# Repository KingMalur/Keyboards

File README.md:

# Keyboards
My personal collection of PCB-designs for keyboards/macroboards. Made in KiCAD.

Untested PCB-designs are going to have a disclaimer in their respective README.

Naming according to this list:
https://www.worldwildlife.org/species/directory?direction=desc&sort=extinction_status

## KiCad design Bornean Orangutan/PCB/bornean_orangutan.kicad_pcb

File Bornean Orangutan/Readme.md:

# Bornean Orangutan
A minimal macroboard aimed to be smaller than 100mmx100mm to qualify for extremely cheap PCB-manufacturing (Since most offer a cheap deal for everything below these values). 

## This PCB is untested and probably not working as intended if at all.

See https://www.worldwildlife.org/species/bornean-orangutan for more information.

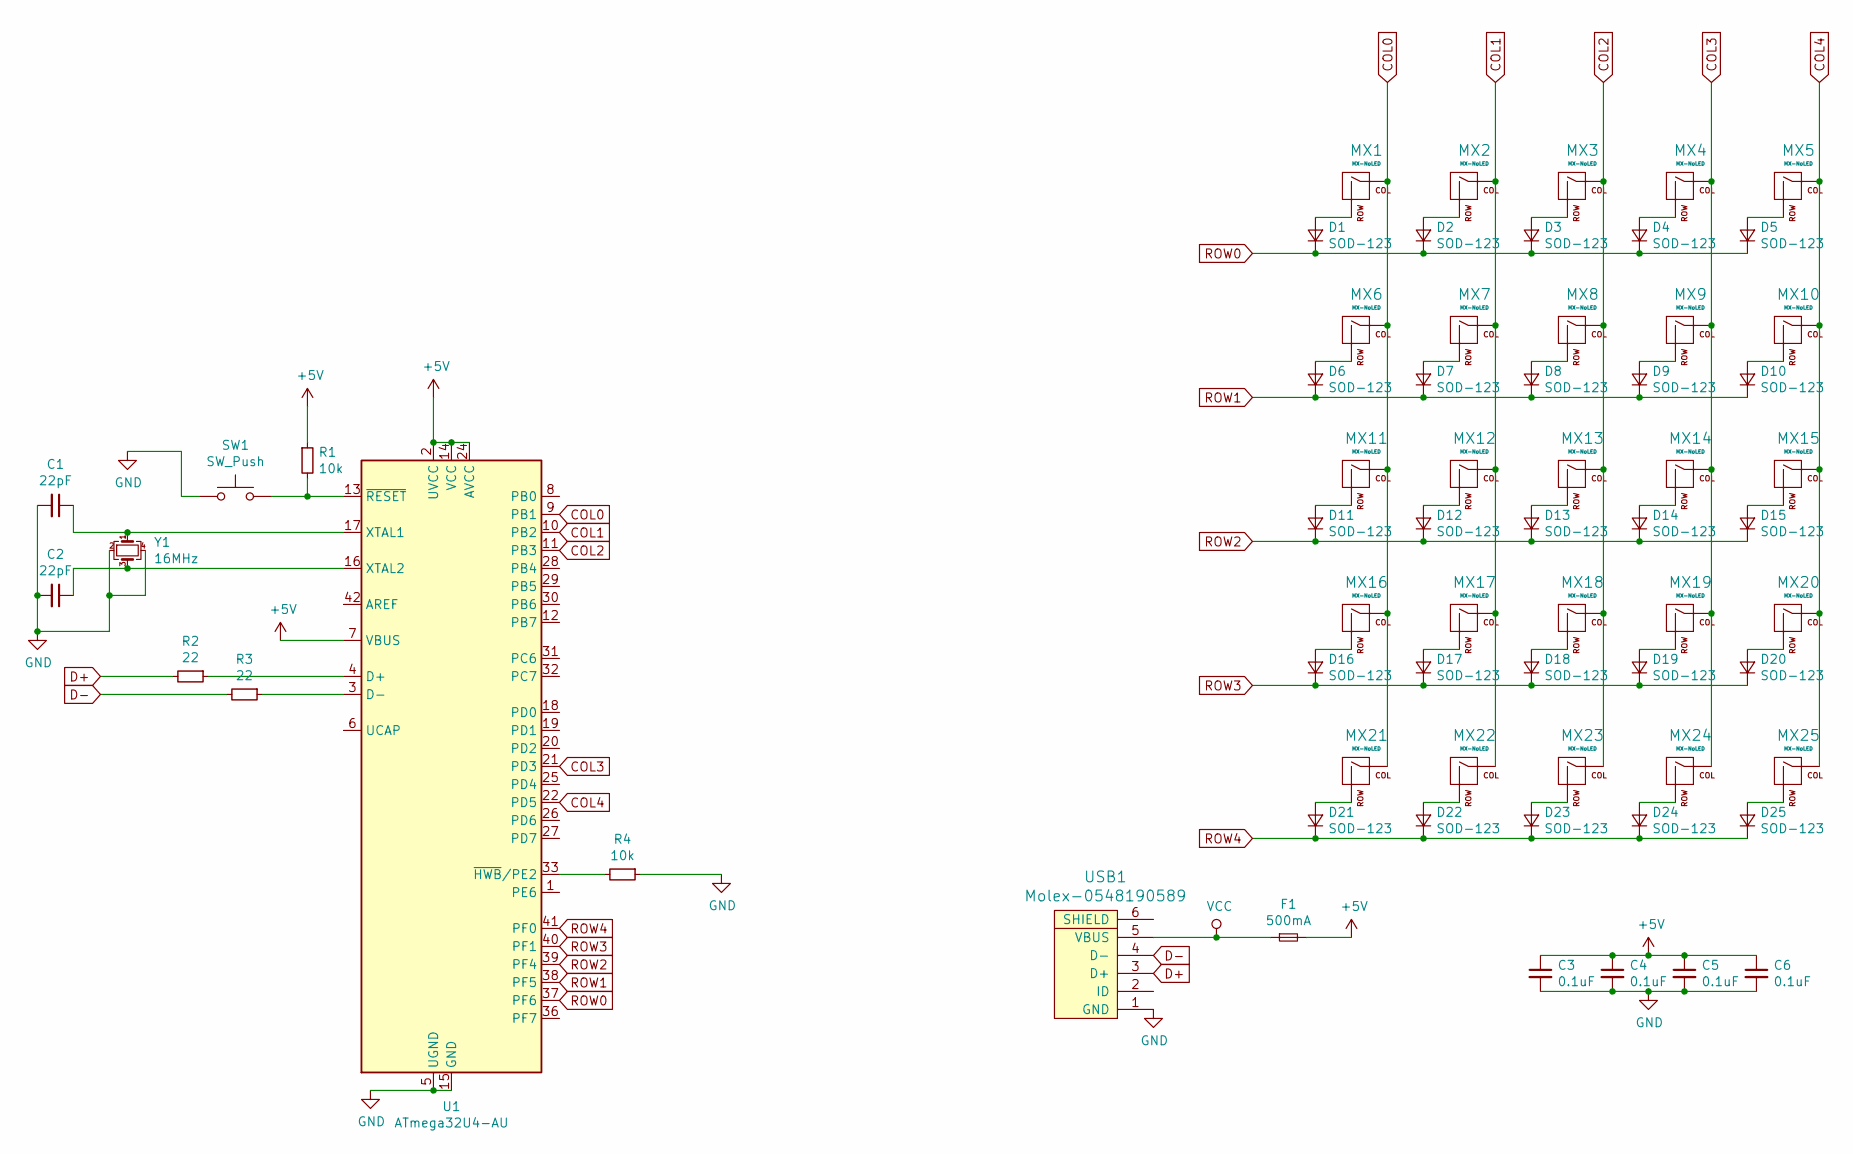
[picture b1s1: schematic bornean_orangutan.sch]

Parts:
C1, C2: 22pF; C_0805_2012Metric
C3, C4, C5, C6: 0.1uF; C_0805_2012Metric
D1, D2, D3, D4, D5, D6, D7, D8, D9, D10, D11, D12, D13, D14, D15, D16, D17, D18, D19, D20, D21, D22, D23, D24, D25: SOD-123; D_SOD-123
F1: 500mA; Fuse_1206_3216Metric
MX1, MX2, MX3, MX4, MX5, MX6, MX7, MX8, MX9, MX10, MX11, MX12, MX13, MX14, MX15, MX16, MX17, MX18, MX19, MX20, MX21, MX22, MX23, MX24, MX25: MX-NoLED; MX-1U
R1, R4: 10k; R_0805_2012Metric
R2, R3: 22; R_0805_2012Metric
SW1: SW_Push; SKQG-1155865
U1: ATmega32U4-AU; TQFP-44_10x10mm_P0.8mm
USB1: Molex-0548190589
Y1: 16MHz; Crystal_SMD_3225-4Pin_3.2x2.5mm

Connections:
+5V: C3.1, C4.1, C5.1, C6.1, F1.2, R1.1, U1.2 (UVCC), U1.7 (VBUS), U1.14 (VCC), U1.24 (AVCC), U1.34 (VCC), U1.44 (AVCC)
COL0: MX1.1 (COL), MX6.1 (COL), MX11.1 (COL), MX16.1 (COL), MX21.1 (COL), U1.9 (PB1)
COL1: MX2.1 (COL), MX7.1 (COL), MX12.1 (COL), MX17.1 (COL), MX22.1 (COL), U1.10 (PB2)
COL2: MX3.1 (COL), MX8.1 (COL), MX13.1 (COL), MX18.1 (COL), MX23.1 (COL), U1.11 (PB3)
COL3: MX4.1 (COL), MX9.1 (COL), MX14.1 (COL), MX19.1 (COL), MX24.1 (COL), U1.21 (PD3)
COL4: MX5.1 (COL), MX10.1 (COL), MX15.1 (COL), MX20.1 (COL), MX25.1 (COL), U1.22 (PD5)
D+: R2.2, USB1.3 (D+)
D-: R3.2, USB1.4 (D-)
GND: C1.2, C2.2, C3.2, C4.2, C5.2, C6.2, R4.1, SW1.1, U1.5 (UGND), U1.15 (GND), U1.23 (GND), U1.35 (GND), U1.43 (GND), USB1.1 (GND), Y1.2, Y1.4
unnamed: C1.1, U1.17 (XTAL1), Y1.1
unnamed: C2.1, U1.16 (XTAL2), Y1.3
unnamed: D1.2 (A), MX1.2 (ROW)
unnamed: D2.2 (A), MX2.2 (ROW)
unnamed: D3.2 (A), MX3.2 (ROW)
unnamed: D4.2 (A), MX4.2 (ROW)
unnamed: D5.2 (A), MX5.2 (ROW)
unnamed: D6.2 (A), MX6.2 (ROW)
unnamed: D7.2 (A), MX7.2 (ROW)
unnamed: D8.2 (A), MX8.2 (ROW)
unnamed: D9.2 (A), MX9.2 (ROW)
unnamed: D10.2 (A), MX10.2 (ROW)
unnamed: D11.2 (A), MX11.2 (ROW)
unnamed: D12.2 (A), MX12.2 (ROW)
unnamed: D13.2 (A), MX13.2 (ROW)
unnamed: D14.2 (A), MX14.2 (ROW)
unnamed: D15.2 (A), MX15.2 (ROW)
unnamed: D16.2 (A), MX16.2 (ROW)
unnamed: D17.2 (A), MX17.2 (ROW)
unnamed: D18.2 (A), MX18.2 (ROW)
unnamed: D19.2 (A), MX19.2 (ROW)
unnamed: D20.2 (A), MX20.2 (ROW)
unnamed: D21.2 (A), MX21.2 (ROW)
unnamed: D22.2 (A), MX22.2 (ROW)
unnamed: D23.2 (A), MX23.2 (ROW)
unnamed: D24.2 (A), MX24.2 (ROW)
unnamed: D25.2 (A), MX25.2 (ROW)
unnamed: R1.2, SW1.2, U1.13 (~RESET)
unnamed: R2.1, U1.4 (D+)
unnamed: R3.1, U1.3 (D-)
unnamed: R4.2, U1.33 (~HWB~/PE2)
ROW0: D1.1 (K), D2.1 (K), D3.1 (K), D4.1 (K), D5.1 (K), U1.37 (PF6)
ROW1: D6.1 (K), D7.1 (K), D8.1 (K), D9.1 (K), D10.1 (K), U1.38 (PF5)
ROW2: D11.1 (K), D12.1 (K), D13.1 (K), D14.1 (K), D15.1 (K), U1.39 (PF4)
ROW3: D16.1 (K), D17.1 (K), D18.1 (K), D19.1 (K), D20.1 (K), U1.40 (PF1)
ROW4: D21.1 (K), D22.1 (K), D23.1 (K), D24.1 (K), D25.1 (K), U1.41 (PF0)
VCC: F1.1, USB1.5 (VBUS)

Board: 2 copper layers, 65 parts (40 on the bottom side), 46 nets, no tracks yet.

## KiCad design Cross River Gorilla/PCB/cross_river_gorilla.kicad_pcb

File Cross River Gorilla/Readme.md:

# Cross River Gorilla
A 60% 5x14 keyboard (64 keys) in ISO-DE (not 100% - obviously - but close since I tried to copy my current 100% ISO-DE keyboard).

## This PCB is untested and probably not working as intended if at all.

See https://www.worldwildlife.org/species/cross-river-gorilla for more information.

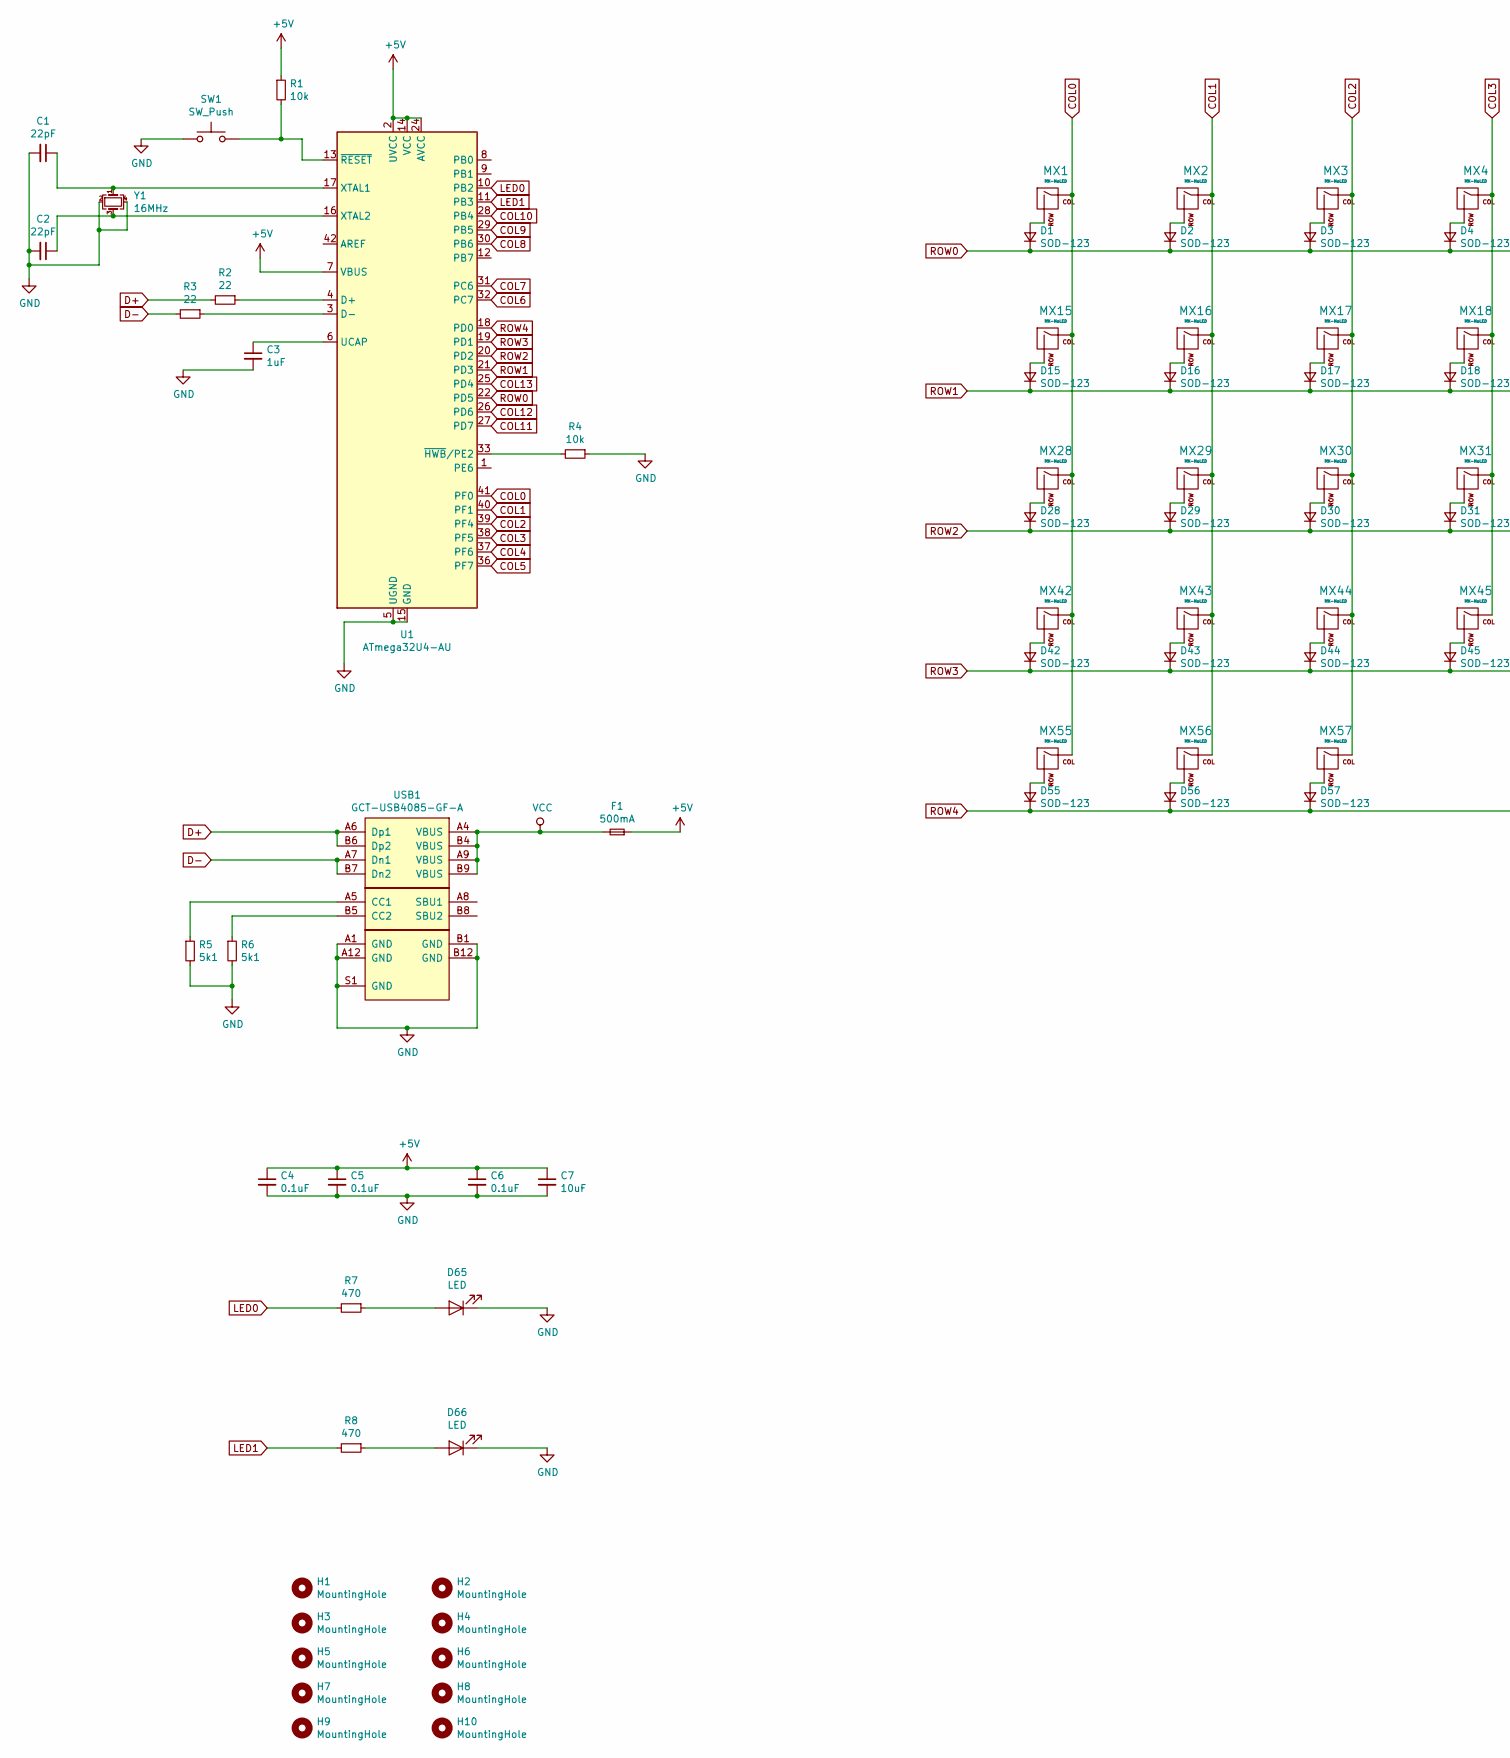
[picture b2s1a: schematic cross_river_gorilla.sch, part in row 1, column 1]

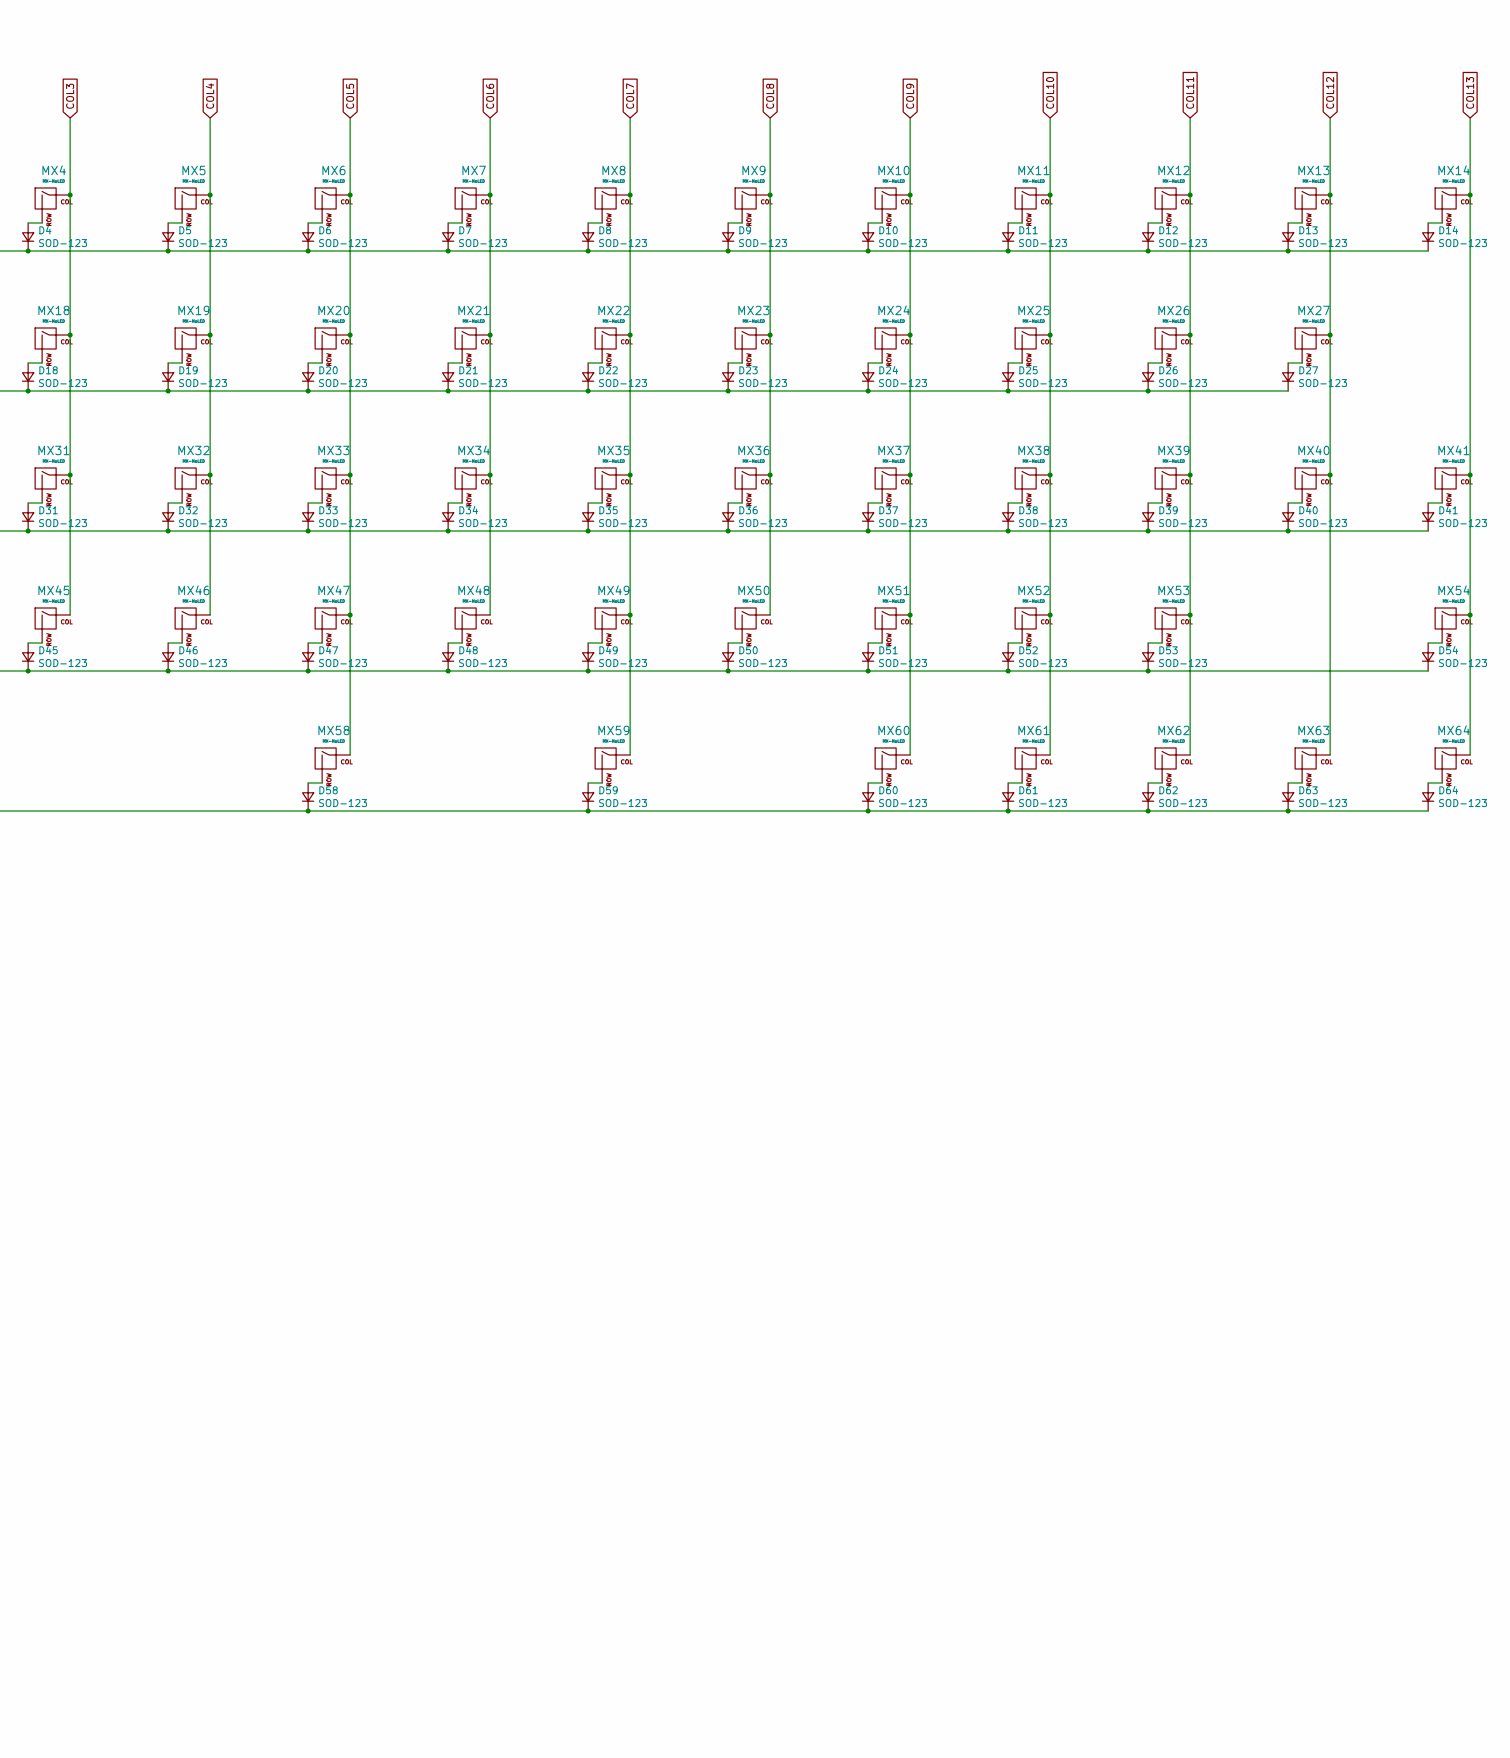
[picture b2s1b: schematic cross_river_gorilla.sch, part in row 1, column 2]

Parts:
C1, C2: 22pF; C_0805_2012Metric
C3: 1uF; C_0805_2012Metric
C4, C5, C6: 0.1uF; C_0805_2012Metric
C7: 10uF; C_0805_2012Metric
D1, D2, D3, D4, D5, D6, D7, D8, D9, D10, D11, D12, D13, D14, D15, D16, D17, D18, D19, D20, D21, D22, D23, D24, D25, D26, D27, D28, D29, D30, D31, D32, D33, D34, D35, D36, D37, D38, D39, D40, D41, D42, D43, D44, D45, D46, D47, D48, D49, D50, D51, D52, D53, D54, D55, D56, D57, D58, D59, D60, D61, D62, D63, D64: SOD-123; D_SOD-123
D65, D66: LED; LED_0805_2012Metric
F1: 500mA; Fuse_1206_3216Metric
H1, H2, H3, H4, H5, H6, H7, H8, H9, H10: MountingHole; MountingHole_2mm
MX1, MX2, MX3, MX4, MX5, MX6, MX7, MX8, MX9, MX10, MX11, MX12, MX13, MX16, MX17, MX18, MX19, MX20, MX21, MX22, MX23, MX24, MX25, MX26, MX27, MX29, MX30, MX31, MX32, MX33, MX34, MX35, MX36, MX37, MX38, MX39, MX40, MX43, MX44, MX45, MX46, MX47, MX48, MX49, MX50, MX51, MX52, MX53, MX60, MX61, MX62, MX63: MX-NoLED; MX-1U
MX14: MX-NoLED; MX-2U
MX15, MX55, MX64: MX-NoLED; MX-1.5U
MX28: MX-NoLED; MX-1.75U
MX41: MX-NoLED; MX-ISO
MX42, MX56, MX57: MX-NoLED; MX-1.25U
MX54, MX58, MX59: MX-NoLED; MX-2.75U
R1, R4: 10k; R_0805_2012Metric
R2, R3: 22; R_0805_2012Metric
R5, R6: 5k1; R_0805_2012Metric
R7, R8: 470; R_0805_2012Metric
SW1: SW_Push; SKQG-1155865
U1: ATmega32U4-AU; TQFP-44_10x10mm_P0.8mm
USB1: GCT-USB4085-GF-A; USB_C_GCT_USB4085
Y1: 16MHz; Crystal_SMD_3225-4Pin_3.2x2.5mm

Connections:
+5V: C4.1, C5.1, C6.1, C7.1, F1.1, R1.1, U1.2 (UVCC), U1.7 (VBUS), U1.14 (VCC), U1.24 (AVCC), U1.34 (VCC), U1.44 (AVCC)
COL0: MX1.1 (COL), MX15.1 (COL), MX28.1 (COL), MX42.1 (COL), MX55.1 (COL), U1.41 (PF0)
COL1: MX2.1 (COL), MX16.1 (COL), MX29.1 (COL), MX43.1 (COL), MX56.1 (COL), U1.40 (PF1)
COL2: MX3.1 (COL), MX17.1 (COL), MX30.1 (COL), MX44.1 (COL), MX57.1 (COL), U1.39 (PF4)
COL3: MX4.1 (COL), MX18.1 (COL), MX31.1 (COL), MX45.1 (COL), U1.38 (PF5)
COL4: MX5.1 (COL), MX19.1 (COL), MX32.1 (COL), MX46.1 (COL), U1.37 (PF6)
COL5: MX6.1 (COL), MX20.1 (COL), MX33.1 (COL), MX47.1 (COL), MX58.1 (COL), U1.36 (PF7)
COL6: MX7.1 (COL), MX21.1 (COL), MX34.1 (COL), MX48.1 (COL), U1.32 (PC7)
COL7: MX8.1 (COL), MX22.1 (COL), MX35.1 (COL), MX49.1 (COL), MX59.1 (COL), U1.31 (PC6)
COL8: MX9.1 (COL), MX23.1 (COL), MX36.1 (COL), MX50.1 (COL), U1.30 (PB6)
COL9: MX10.1 (COL), MX24.1 (COL), MX37.1 (COL), MX51.1 (COL), MX60.1 (COL), U1.29 (PB5)
COL10: MX11.1 (COL), MX25.1 (COL), MX38.1 (COL), MX52.1 (COL), MX61.1 (COL), U1.28 (PB4)
COL11: MX12.1 (COL), MX26.1 (COL), MX39.1 (COL), MX53.1 (COL), MX62.1 (COL), U1.27 (PD7)
COL12: MX13.1 (COL), MX27.1 (COL), MX40.1 (COL), MX63.1 (COL), U1.26 (PD6)
COL13: MX14.1 (COL), MX41.1 (COL), MX54.1 (COL), MX64.1 (COL), U1.25 (PD4)
D+: R2.2, USB1.A6 (Dp1), USB1.B6 (Dp2)
D-: R3.2, USB1.A7 (Dn1), USB1.B7 (Dn2)
GND: C1.2, C2.2, C3.2, C4.2, C5.2, C6.2, C7.2, D65.1 (K), D66.1 (K), R4.1, R5.2, R6.2, SW1.1, U1.5 (UGND), U1.15 (GND), U1.23 (GND), U1.35 (GND), U1.43 (GND), USB1.A1 (GND), USB1.A12 (GND), USB1.B1 (GND), USB1.B12 (GND), USB1.S1 (GND), Y1.2, Y1.4
LED0: R7.2, U1.10 (PB2)
LED1: R8.2, U1.11 (PB3)
unnamed: C1.1, U1.17 (XTAL1), Y1.1
unnamed: C2.1, U1.16 (XTAL2), Y1.3
unnamed: C3.1, U1.6 (UCAP)
unnamed: D1.2 (A), MX1.2 (ROW)
unnamed: D2.2 (A), MX2.2 (ROW)
unnamed: D3.2 (A), MX3.2 (ROW)
unnamed: D4.2 (A), MX4.2 (ROW)
unnamed: D5.2 (A), MX5.2 (ROW)
unnamed: D6.2 (A), MX6.2 (ROW)
unnamed: D7.2 (A), MX7.2 (ROW)
unnamed: D8.2 (A), MX8.2 (ROW)
unnamed: D9.2 (A), MX9.2 (ROW)
unnamed: D10.2 (A), MX10.2 (ROW)
unnamed: D11.2 (A), MX11.2 (ROW)
unnamed: D12.2 (A), MX12.2 (ROW)
unnamed: D13.2 (A), MX13.2 (ROW)
unnamed: D14.2 (A), MX14.2 (ROW)
unnamed: D15.2 (A), MX15.2 (ROW)
unnamed: D16.2 (A), MX16.2 (ROW)
unnamed: D17.2 (A), MX17.2 (ROW)
unnamed: D18.2 (A), MX18.2 (ROW)
unnamed: D19.2 (A), MX19.2 (ROW)
unnamed: D20.2 (A), MX20.2 (ROW)
unnamed: D21.2 (A), MX21.2 (ROW)
unnamed: D22.2 (A), MX22.2 (ROW)
unnamed: D23.2 (A), MX23.2 (ROW)
unnamed: D24.2 (A), MX24.2 (ROW)
unnamed: D25.2 (A), MX25.2 (ROW)
unnamed: D26.2 (A), MX26.2 (ROW)
unnamed: D27.2 (A), MX27.2 (ROW)
unnamed: D28.2 (A), MX28.2 (ROW)
unnamed: D29.2 (A), MX29.2 (ROW)
unnamed: D30.2 (A), MX30.2 (ROW)
unnamed: D31.2 (A), MX31.2 (ROW)
unnamed: D32.2 (A), MX32.2 (ROW)
unnamed: D33.2 (A), MX33.2 (ROW)
unnamed: D34.2 (A), MX34.2 (ROW)
unnamed: D35.2 (A), MX35.2 (ROW)
unnamed: D36.2 (A), MX36.2 (ROW)
unnamed: D37.2 (A), MX37.2 (ROW)
unnamed: D38.2 (A), MX38.2 (ROW)
unnamed: D39.2 (A), MX39.2 (ROW)
unnamed: D40.2 (A), MX40.2 (ROW)
unnamed: D41.2 (A), MX41.2 (ROW)
unnamed: D42.2 (A), MX42.2 (ROW)
unnamed: D43.2 (A), MX43.2 (ROW)
unnamed: D44.2 (A), MX44.2 (ROW)
unnamed: D45.2 (A), MX45.2 (ROW)
unnamed: D46.2 (A), MX46.2 (ROW)
unnamed: D47.2 (A), MX47.2 (ROW)
unnamed: D48.2 (A), MX48.2 (ROW)
unnamed: D49.2 (A), MX49.2 (ROW)
unnamed: D50.2 (A), MX50.2 (ROW)
unnamed: D51.2 (A), MX51.2 (ROW)
unnamed: D52.2 (A), MX52.2 (ROW)
unnamed: D53.2 (A), MX53.2 (ROW)
unnamed: D54.2 (A), MX54.2 (ROW)
unnamed: D55.2 (A), MX55.2 (ROW)
unnamed: D56.2 (A), MX56.2 (ROW)
unnamed: D57.2 (A), MX57.2 (ROW)
unnamed: D58.2 (A), MX58.2 (ROW)
unnamed: D59.2 (A), MX59.2 (ROW)
unnamed: D60.2 (A), MX60.2 (ROW)
unnamed: D61.2 (A), MX61.2 (ROW)
unnamed: D62.2 (A), MX62.2 (ROW)
unnamed: D63.2 (A), MX63.2 (ROW)
unnamed: D64.2 (A), MX64.2 (ROW)
unnamed: D65.2 (A), R7.1
unnamed: D66.2 (A), R8.1
unnamed: R1.2, SW1.2, U1.13 (~RESET)
unnamed: R2.1, U1.4 (D+)
unnamed: R3.1, U1.3 (D-)
unnamed: R4.2, U1.33 (~HWB~/PE2)
unnamed: R5.1, USB1.A5 (CC1)
unnamed: R6.1, USB1.B5 (CC2)
ROW0: D1.1 (K), D2.1 (K), D3.1 (K), D4.1 (K), D5.1 (K), D6.1 (K), D7.1 (K), D8.1 (K), D9.1 (K), D10.1 (K), D11.1 (K), D12.1 (K), D13.1 (K), D14.1 (K), U1.22 (PD5)
ROW1: D15.1 (K), D16.1 (K), D17.1 (K), D18.1 (K), D19.1 (K), D20.1 (K), D21.1 (K), D22.1 (K), D23.1 (K), D24.1 (K), D25.1 (K), D26.1 (K), D27.1 (K), U1.21 (PD3)
ROW2: D28.1 (K), D29.1 (K), D30.1 (K), D31.1 (K), D32.1 (K), D33.1 (K), D34.1 (K), D35.1 (K), D36.1 (K), D37.1 (K), D38.1 (K), D39.1 (K), D40.1 (K), D41.1 (K), U1.20 (PD2)
ROW3: D42.1 (K), D43.1 (K), D44.1 (K), D45.1 (K), D46.1 (K), D47.1 (K), D48.1 (K), D49.1 (K), D50.1 (K), D51.1 (K), D52.1 (K), D53.1 (K), D54.1 (K), U1.19 (PD1)
ROW4: D55.1 (K), D56.1 (K), D57.1 (K), D58.1 (K), D59.1 (K), D60.1 (K), D61.1 (K), D62.1 (K), D63.1 (K), D64.1 (K), U1.18 (PD0)
VCC: F1.2, USB1.A4 (VBUS), USB1.A9 (VBUS), USB1.B4 (VBUS), USB1.B9 (VBUS)

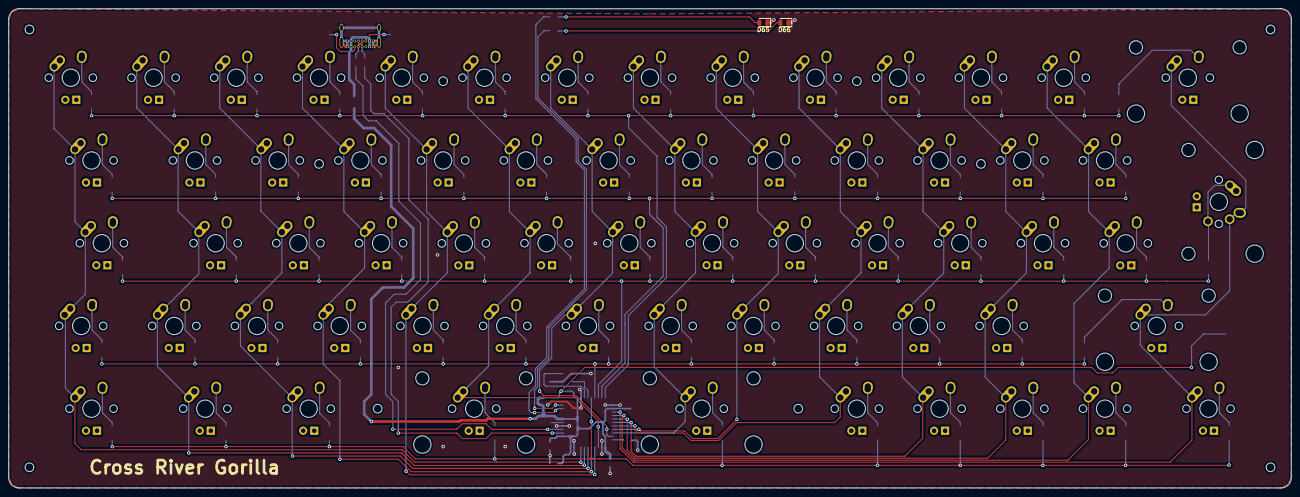
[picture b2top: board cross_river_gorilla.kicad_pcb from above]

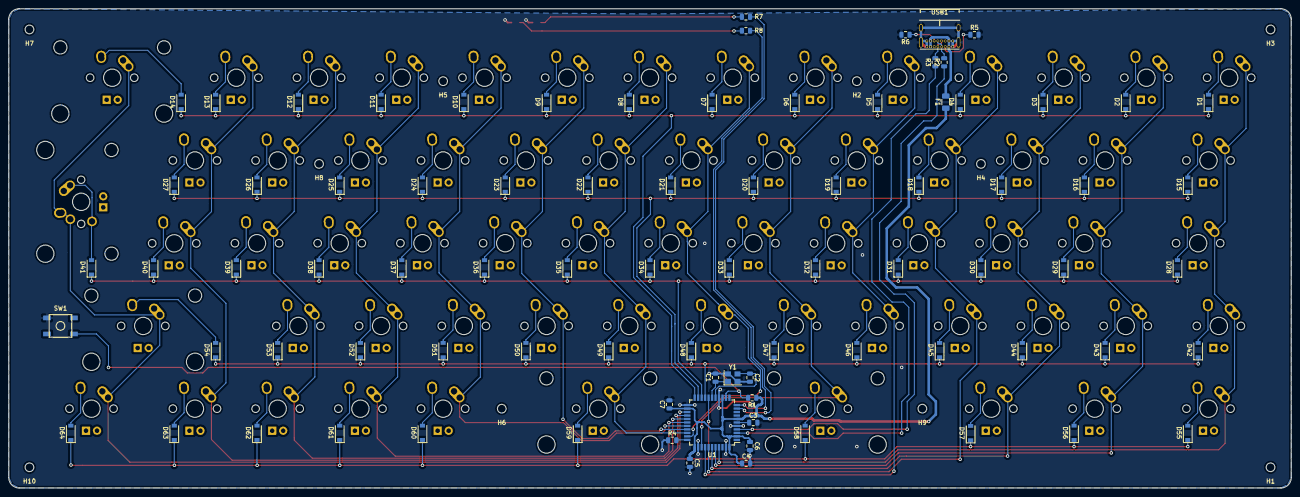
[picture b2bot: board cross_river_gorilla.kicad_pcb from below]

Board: 2 copper layers, 295.3 x 110.3 mm, 160 parts (94 on the bottom side), 101 nets.

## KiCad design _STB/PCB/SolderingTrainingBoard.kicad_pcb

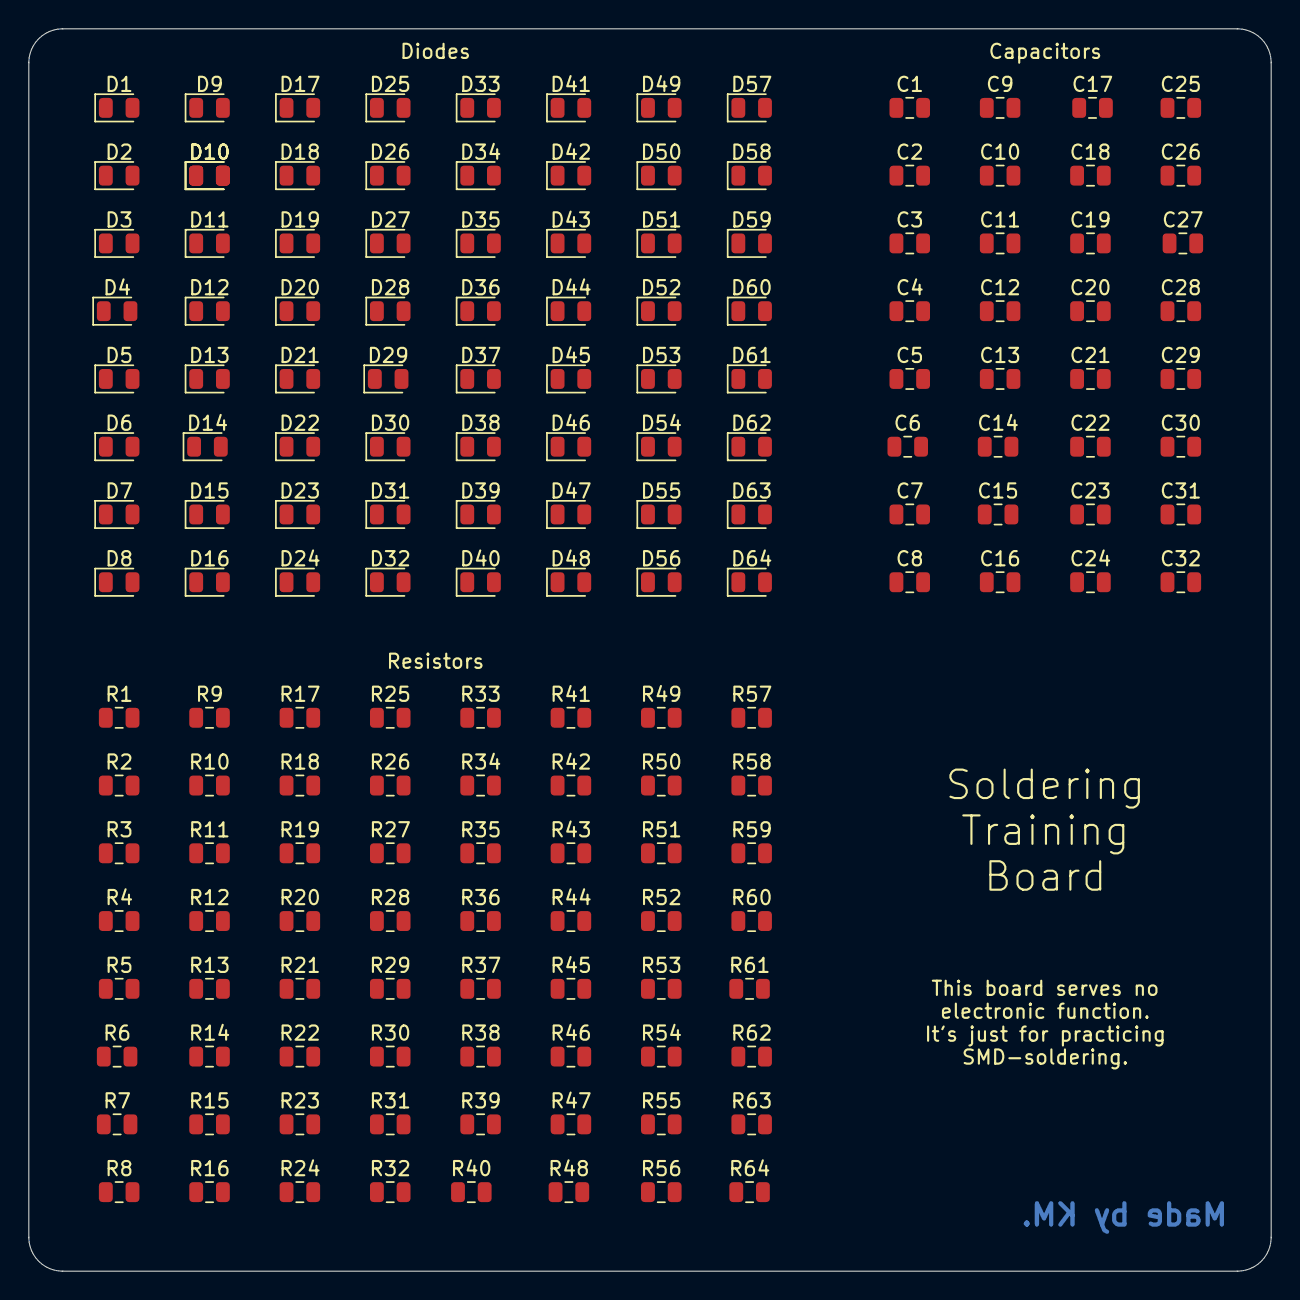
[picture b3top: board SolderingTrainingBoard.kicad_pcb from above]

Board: 2 copper layers, 87.3 x 87.3 mm, 161 parts (0 on the bottom side), 2 nets, no tracks yet.

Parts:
C1, C2, C3, C4, C5, C6, C7, C8, C9, C10, C11, C12, C13, C14, C15, C16, C17, C18, C19, C20, C21, C22, C23, C24, C25, C26, C27, C28, C29, C30, C31, C32: C_Small; C_0805_2012Metric
D1, D2, D3, D4, D5, D6, D7, D8, D9, D10, D10#2, D11, D12, D13, D14, D15, D16, D17, D18, D19, D20, D21, D22, D23, D24, D25, D26, D27, D28, D29, D30, D31, D32, D33, D34, D35, D36, D37, D38, D39, D40, D41, D42, D43, D44, D45, D46, D47, D48, D49, D50, D51, D52, D53, D54, D55, D56, D57, D58, D59, D60, D61, D62, D63, D64: D_Small; D_0805_2012Metric
R1, R2, R3, R4, R5, R6, R7, R8, R9, R10, R11, R12, R13, R14, R15, R16, R17, R18, R19, R20, R21, R22, R23, R24, R25, R26, R27, R28, R29, R30, R31, R32, R33, R34, R35, R36, R37, R38, R39, R40, R41, R42, R43, R44, R45, R46, R47, R48, R49, R50, R51, R52, R53, R54, R55, R56, R57, R58, R59, R60, R61, R62, R63, R64: R_Small; R_0805_2012Metric

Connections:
unnamed: D10.1, D10#2.1
unnamed: D10.2, D10#2.2

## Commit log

2020-07-29 Initial Commit & Add Amur Leopard
2020-07-29 Improve Amur Leopard-PCB & -Schema
2020-07-29 Improve Amur Leopard-PCB
2020-07-29 Improve Amur Leopard-PCB & Add Decorations
2020-07-30 Add Black Rhino
2020-07-30 Add Black Rhino-PCB
2020-07-30 Wire Black-Rhino-PCB
2020-07-30 Improve Black-Rhino-PCB & Add MountingHoles
2020-07-30 Add MountingHoles to Amur Leopard
2020-07-30 Fix Black Rhino-PCB & -MountingHoles
2020-07-30 Change Black Rhino-PCB & Change Amur Leopard Libs
2020-08-02 Add Indicator-LEDs to Black Rhino
2020-08-02 Add Ohms to LED-Resistors of Black Rhino
2020-08-02 Fix Black Rhino-PCB
    I only needed 1 Indicator-LED and added 3 in commit:
    67b9c5aa973747f4bc26af49aa7426545263447c
2020-08-02 Add .gitignore for Gerber-Files
2020-08-02 Improve Black Rhino-PCB
2020-08-02 Update Black Rhino-Readme
2020-08-02 Update Black Rhino-Schematic
2020-08-02 Update Readmes
2020-08-06 Fix Black Rhino-Traces
2020-08-09 Rewire Black Rhino-PCB
2020-08-09 Add Soldering Training Board
2020-08-09 Add Black Rhino-Layout
2020-08-09 Add Bornean Orangutan
2020-08-12 Update Bornean Orangutan-Schematic & -PCB
2020-08-12 Add USB-C to Black Rhino
2020-08-13 Update Submodules
2020-08-13 Update Black Rhino-PCB
    USB-C from commit
    4d49d241aeb4ff990ef37ecb95a9e68bcacd4131
    is implemented with this commit.
2020-08-13 Update Black Rhino-PCB
2020-08-13 Add Mouting Plate to Black Rhino
2020-08-14 Add Black Rhino-Base & Improve Black Rhino-PCB
2020-08-30 Fix Typo in STB-Silkscreen
2020-08-30 Add Cross River Gorilla
    This is going to be a minimal keyboard or maybe a keypad only.
2020-08-30 Update Black Rhino-Key Layout
2020-08-30 Add Cross River Gorilla-Project
2020-08-30 Improve Cross River Gorilla-PCB
2022-03-13 Rename README
